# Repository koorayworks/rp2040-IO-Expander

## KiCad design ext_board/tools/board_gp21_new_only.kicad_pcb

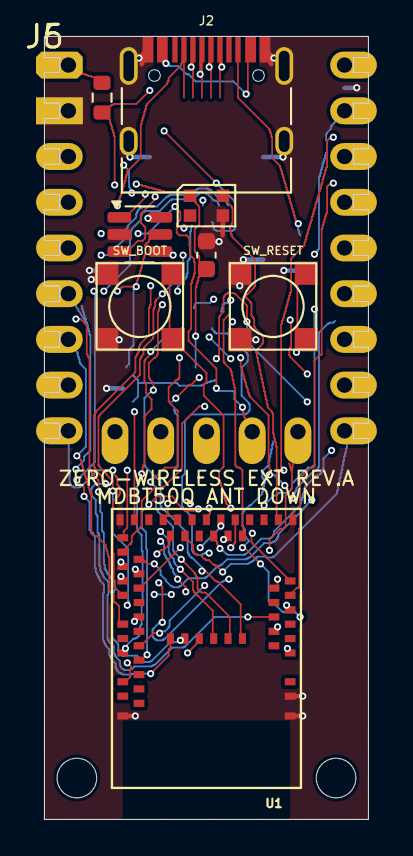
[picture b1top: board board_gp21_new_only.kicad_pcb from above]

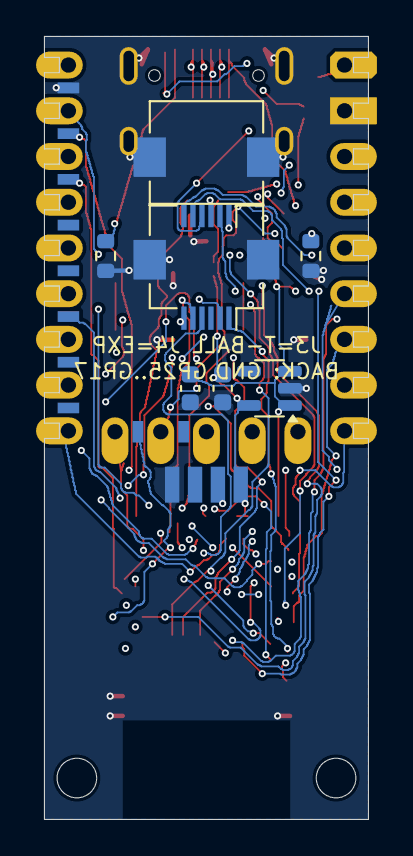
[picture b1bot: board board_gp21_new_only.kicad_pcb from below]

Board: 4 copper layers, 18.0 x 43.5 mm, 20 parts (7 on the bottom side), 56 nets.

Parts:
C1: 10uF IN; C_0603_1608Metric
C2: 10uF OUT; C_0603_1608Metric
C3: 100nF; C_0603_1608Metric
D1: USBLC6-2SC6; SOT-23-6
D2: WS2812B-2020; LED_WS2812B-2020_PLCC4_2.0x2.0mm
J2: TYPE-C-31-M-12
J3: FFC6 TB; Hirose_FH12-6S-0.5SH_1x06-1MP_P0.50mm_Horizontal
J4: FFC6 EXP; Hirose_FH12-6S-0.5SH_1x06-1MP_P0.50mm_Horizontal
J5: SWD
J6: BACKPADS GP17-25
JLEG: RP2040-Zero-THT; RP2040-Zero-THT-Castellation-Master
MH1, MH2: M2; MountingHole_2.2mm_M2
R1: 5.1k CC1; R_0603_1608Metric
R2: 5.1k CC2; R_0603_1608Metric
R3: 0R VBUS->VSYS; R_0603_1608Metric
SW_BOOT: TS-1187A-B-A-B / C318884; SW-SMD_4P-L5.1-W5.1-P3.70-LS6.5-TL_H1.5
SW_RESET: TS-1187A-B-A-B / C318884; SW-SMD_4P-L5.1-W5.1-P3.70-LS6.5-TL_H1.5
U1: MDBT50Q-1MV2; MDBT50Q
U2: TPS7A2033PDBVR; SOT-23-5

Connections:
3V3: C2.1, C3.1, D2.1, J5.1, JLEG.30, U1.28, U1.30, U2.5
BOOT: SW_BOOT.2, SW_BOOT.3, U1.14
CC1: J2.A5, R1.1
CC2: J2.B5, R2.1
EX1: J4.1, U1.48
EX2: J4.2, U1.49
EX3: J4.3, U1.50
EX4: J4.4, U1.47
EX5: J4.5, U1.19
EX6: J4.6, U1.10
GND: C1.2, C2.2, C3.2, D1.2, D2.3, J2.A1, J2.A12, J2.B1, J2.B12, J2.S1, J3.MP, J4.MP, J5.4, J6.1, JLEG.31, R1.2, R2.2, SW_BOOT.1, SW_BOOT.4, SW_RESET.1, SW_RESET.4, U1.1, U1.2, U1.15, U1.33, U1.55, U2.2
GP17: J6.10, U1.3
GP18: J6.9, U1.4
GP19: J6.8, U1.5
GP20: J6.7, U1.6
GP21: J6.6, U1.7
GP22: J6.5, U1.8
GP23: J6.4, U1.11
GP24: J6.3, U1.12
GP25: J6.2, U1.13
GPIO0: JLEG.0, U1.9
GPIO1: JLEG.1, U1.20
GPIO2: JLEG.2, U1.21
GPIO3: JLEG.3, U1.22
GPIO4: JLEG.4, U1.23
GPIO5: JLEG.5, U1.24
GPIO6: JLEG.6, U1.25
GPIO7: JLEG.7, U1.26
GPIO8: JLEG.8, U1.27
GPIO9: JLEG.9, U1.29
GPIO10: JLEG.10, U1.37
GPIO11: JLEG.11, U1.36
GPIO12: JLEG.12, U1.39
GPIO13: JLEG.13, U1.38
GPIO14: JLEG.14, U1.41
GPIO15: JLEG.15, U1.42
GPIO26: JLEG.26, U1.44
GPIO27: JLEG.27, U1.43
GPIO28: JLEG.28, U1.46
GPIO29: JLEG.29, U1.45
RESET: SW_RESET.2, SW_RESET.3, U1.40
STATUS_LED: D2.4, U1.16
SWDCLK: J5.3, U1.53
SWDIO: J5.2, U1.51
TB1: J3.1, U1.56
TB2: J3.2, U1.57
TB3: J3.3, U1.58
TB4: J3.4, U1.59
TB5: J3.5, U1.60
TB6: J3.6, U1.61
USB_D+: D1.4, U1.35
USB_D+_C: D1.3, J2.A6, J2.B6
USB_D-: D1.6, U1.34
USB_D-_C: D1.1, J2.A7, J2.B7
USB_VBUS: C1.1, D1.5, J2.A4, J2.A9, J2.B4, J2.B9, R3.1, U1.32, U2.1, U2.3
VSYS: JLEG.32, R3.2

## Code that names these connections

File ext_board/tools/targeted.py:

#!/usr/bin/env python3
"""Targeted routing for the remaining unrouted nets (post-heal state).
CC2 is ripped and redone (its path violated the USB-C NPTH hole clearance;
the router model now blocks those holes)."""
import pcbnew, os, math, time, sys
import importlib.util

HERE = os.path.dirname(os.path.abspath(__file__))
spec = importlib.util.spec_from_file_location("router", os.path.join(HERE, "router.py"))
rt = importlib.util.module_from_spec(spec)
sys.argv = ["targeted"]
spec.loader.exec_module(rt)
PATH = os.path.expanduser("~/workspace/projects/rp2040-IO-Expander/ext_board/ext_board.kicad_pcb")

ORDER = ["CC2", "USB_D-_C", "USB_D-", "USB_D+", "EX5", "RESET",
         "GP24", "GP25", "GPIO12", "GPIO15", "GPIO26", "GPIO27",
         "GPIO7", "GPIO2", "GPIO1", "GPIO0",
         "TB1", "TB2", "TB5", "TB6", "USB_VBUS"]

def main():
    b = pcbnew.LoadBoard(PATH)
    r = rt.R(b)
    r.ingest()
    t0 = time.time()
    if "CC2" in r.geom:
        r.ripup("CC2")
        print("ripped CC2", flush=True)
    for name in ORDER:
        if r.net_components(name) <= 1:
            print(f"SKIP {name}: already connected", flush=True)
            continue
        ok = r.route_net(name, via_cost=2.0, max_exp=350000) and r.net_components(name) <= 1
        if not ok:
            if name in r.geom:
                r.ripup(name)
            blockers = rt.corridor_blockers(r, name, set())
            for blk in blockers[:2]:
                r.ripup(blk)
                if r.route_net(name, via_cost=2.0, max_exp=500000) and r.net_components(name) <= 1:
                    if not (r.route_net(blk, via_cost=2.0, max_exp=350000) and r.net_components(blk) <= 1):
                        print(f"  note: {blk} sacrificed for {name}", flush=True)
                    ok = True
                    break
                else:
                    if name in r.geom:
                        r.ripup(name)
                    r.route_net(blk, via_cost=2.0, max_exp=350000)
        print(f"{name}: {'OK' if ok else 'FAIL'} ({time.time()-t0:.0f}s)", flush=True)
        if ok:
            pcbnew.SaveBoard(PATH, b)
    pcbnew.SaveBoard(PATH, b)
    left = [n for n in ORDER if r.net_components(n) > 1]
    print("STILL_UNROUTED:", left, flush=True)
    print("TARGETED DONE", flush=True)

if __name__ == "__main__":
    main()

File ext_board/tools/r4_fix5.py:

#!/usr/bin/env python3
"""Round 4 fix 5 (geometry from measured pad map, south-central is empty
on B.Cu except C1/C2; SJ1/SJ2 are NOT in this area):
- GPIO0 v11: F.Cu east column to (14.53,17.60), diagonal to via (15.70,18.70)
  (In2 sum 34.40 clears GPIO6/GPIO7 diagonal pair; 0.56 from GP21 via),
  B.Cu east loop via (16.90,19.20) staying clear of J6 GP20/GP19 pads,
  via_bot (13.50,20.85).
- RESET v3: F.Cu south-edge exit to via (13.13,19.12) (clears RESET pad1,
  C1 pad1 corner, GPIO4 via, GPIO2 F column), B.Cu east run to via
  (15.60,19.60), F.Cu stub into the existing south chain at (15.39,20.12).
  Old east route and its tail segment removed.
- USB_D- v6: restore original In2 diagonal, via (5.12,16.85), F.Cu column
  x=5.12 (0.135 east of new BOOT pad2, west of D+ x=5.56), jog to the
  original x=5.2007 south column, reconnecting the kept south stub.
- Delete leftover GPIO2 via at (13.10,19.10) from fix3.
"""
import pcbnew

IU = pcbnew.FromMM(1)
P = 'ext_board.kicad_pcb'
bd = pcbnew.LoadBoard(P)
L_F, L_IN2, L_B = 0, 2, 31
NETC = bd.GetNetInfo()
TOL = 0.06

def v2(x, y):
    return pcbnew.VECTOR2I(int(round(x * IU)), int(round(y * IU)))

def close(a, b):
    return abs(a[0] - b[0]) <= TOL and abs(a[1] - b[1]) <= TOL

def seg_key(t):
    s, e = t.GetStart(), t.GetEnd()
    return (s.x / IU, s.y / IU), (e.x / IU, e.y / IU)

tracks = list(bd.GetTracks())

DEL_SEG = [
    ('GPIO0', L_F, (14.53, 16.55), (14.53, 16.90)),
    ('GPIO0', L_F, (14.53, 16.90), (12.90, 16.90)),
    ('GPIO0', L_F, (12.90, 16.90), (12.42, 17.50)),
    ('GPIO0', L_B, (12.42, 17.50), (13.45, 17.45)),
    ('GPIO0', L_B, (13.45, 17.45), (13.28, 19.60)),
    ('GPIO0', L_B, (13.28, 19.60), (13.50, 20.85)),
    ('GPIO0', L_F, (13.50, 20.85), (13.37, 20.80)),
    ('RESET', L_F, (13.90, 18.05), (14.88, 18.35)),
    ('RESET', L_F, (14.88, 18.35), (14.88, 19.62)),
    ('RESET', L_F, (14.88, 19.62), (15.39, 20.12)),
    ('USB_D-', L_IN2, (4.2925, 15.9237), (4.45, 16.60)),
    ('USB_D-', L_B, (4.45, 16.60), (4.90, 17.70)),
    ('USB_D-', L_B, (4.90, 17.70), (4.90, 19.50)),
    ('USB_D-', L_F, (4.90, 19.50), (4.90, 23.90)),
    ('USB_D-', L_F, (4.90, 23.90), (5.20, 24.09)),
]
DEL_VIA = [
    ('GPIO0', (12.42, 17.50)),
    ('GPIO0', (13.50, 20.85)),
    ('GPIO2', (13.10, 19.10)),
    ('USB_D-', (4.45, 16.60)),
    ('USB_D-', (4.90, 19.50)),
]

to_remove = []
for net, layer, p1, p2 in DEL_SEG:
    hit = None
    for t in tracks:
        if t.GetClass() == 'PCB_VIA' or t in to_remove:
            continue
        if t.GetNetname() != net or t.GetLayer() != layer:
            continue
        a, b = seg_key(t)
        if (close(a, p1) and close(b, p2)) or (close(a, p2) and close(b, p1)):
            hit = t
            break
    if hit is None:
        print('WARN seg not found:', net, layer, p1, p2)
    else:
        to_remove.append(hit)
for net, pos in DEL_VIA:
    hit = None
    for t in tracks:
        if t.GetClass() != 'PCB_VIA' or t in to_remove:
            continue
        if t.GetNetname() != net:
            continue
        s = t.GetStart()
        if close((s.x / IU, s.y / IU), pos):
            hit = t
            break
    if hit is None:
        print('WARN via not found:', net, pos)
    else:
        to_remove.append(hit)
for t in to_remove:
    bd.Remove(t)
print('removed', len(to_remove), 'items')

def add_seg(net, layer, p1, p2, w=0.10):
    s = pcbnew.PCB_TRACK(bd)
    s.SetNet(NETC.GetNetItem(net))
    s.SetLayer(layer)
    s.SetStart(v2(*p1))
    s.SetEnd(v2(*p2))
    s.SetWidth(int(round(w * IU)))
    bd.Add(s)

def add_via(net, pos):
    v = pcbnew.PCB_VIA(bd)
    v.SetNet(NETC.GetNetItem(net))
    v.SetPosition(v2(*pos))
    v.SetDrill(int(round(0.20 * IU)))
    v.SetWidth(int(round(0.40 * IU)))
    v.SetViaType(pcbnew.VIATYPE_THROUGH)
    bd.Add(v)

ADD_SEG = [
    # GPIO0 v11
    ('GPIO0', L_F, (14.53, 16.55), (14.53, 17.60), 0.10),
    ('GPIO0', L_F, (14.53, 17.60), (15.70, 18.70), 0.10),
    ('GPIO0', L_B, (15.70, 18.70), (16.90, 19.20), 0.10),
    ('GPIO0', L_B, (16.90, 19.20), (14.45, 20.75), 0.10),
    ('GPIO0', L_B, (14.45, 20.75), (13.50, 20.85), 0.10),
    ('GPIO0', L_F, (13.50, 20.85), (13.37, 20.80), 0.10),
    # RESET v3
    ('RESET', L_F, (13.35, 18.81), (13.13, 19.12), 0.10),
    ('RESET', L_B, (13.13, 19.12), (14.60, 19.22), 0.10),
    ('RESET', L_B, (14.60, 19.22), (15.60, 19.60), 0.10),
    ('RESET', L_F, (15.60, 19.60), (15.39, 20.12), 0.10),
    # USB_D- v6
    ('USB_D-', L_IN2, (4.2925, 15.9237), (5.0692, 16.7004), 0.10),
    ('USB_D-', L_IN2, (5.0692, 16.7004), (5.12, 16.85), 0.10),
    ('USB_D-', L_F, (5.12, 16.85), (5.12, 19.15), 0.10),
    ('USB_D-', L_F, (5.12, 19.15), (5.2007, 19.30), 0.10),
    ('USB_D-', L_F, (5.2007, 19.30), (5.2007, 24.0948), 0.10),
]
ADD_VIA = [
    ('GPIO0', (15.70, 18.70)),
    ('GPIO0', (13.50, 20.85)),
    ('RESET', (13.13, 19.12)),
    ('RESET', (15.60, 19.60)),
    ('USB_D-', (5.12, 16.85)),
]
for net, layer, p1, p2, w in ADD_SEG:
    add_seg(net, layer, p1, p2, w)
for net, pos in ADD_VIA:
    add_via(net, pos)
print('added', len(ADD_SEG), 'segs,', len(ADD_VIA), 'vias')

filler = pcbnew.ZONE_FILLER(bd)
filler.Fill(bd.Zones())
bd.Save(P)
print('saved')
